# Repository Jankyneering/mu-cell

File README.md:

<h1 align="center">µCell</h1>

<p align="center">An open-source SDR base station platform for digital and analog voice modes.</p>

Got a board? Start with the [Quick Start Guide](docs/quickStartGuide.md).

---

## Contents

- [What is µCell?](#what-is-µcell)
- [Where to Buy](#where-to-buy)
- [Build Your Own](#build-your-own)
- [How the Software Fits Together](#how-the-software-fits-together)
- [Documentation](#documentation)
- [How to Contribute](#how-to-contribute)
- [Acknowledgements & License](#acknowledgements--license)

---

## What is µCell?

µCell is a software-defined radio base station/repeater/transceiver that runs on a Raspberry Pi.

The µCell BB board puts an SX1255 transceiver, its RF front-end, and a HAT identification EEPROM on a board that sits on a Pi 3, 4, 5, or Zero 2W. A single command installs the driver, and from there you pick the radio software you want to run.

The board presents itself as a standard SoapySDR device. The project started with TETRA, but DMR, D-Star, YSF, P25, and analog FM run on the same board through MMDVM-IQ, and general-purpose SDR software works with it directly. The goal is to support every voice mode we can reach.

Everything is open. Schematics, PCB layouts, production outputs, 3D printed case designs, drivers, and the EEPROM tooling are all in this repository, under licences that let you build, modify, and sell your own.

---

## Where to Buy

Assembled and tested µCell BB boards are sold by Fred Corp., one half of the Jankyneering team:

[store.fredcorp.cc](http://store.fredcorp.cc/)

Each board sold there is individually measured on an RF test set before shipping, and carries a signed EEPROM so the driver can confirm where it came from. See the [FAQ](docs/faq.md) for what signing does and does not mean.

---

## Build Your Own

The design is open and the production outputs are in this repository, ready to upload to a PCBA house. Component choice is critical: the RF path depends on inductor Q, capacitor dielectric, and a low drift referenceL. Foregoing proper part selection will affect sensitivity and output power.

See [docs/muCellBBManufacture.md](docs/muCellBBManufacture.md) for the production package contents, the stackup, the component selection notes, and the EEPROM writing procedure.

---

## Software structure

The stack has three layers.

### 1. µCell BB drivers

[mu-cell-bb-drivers](https://github.com/Jankyneering/mu-cell-bb-drivers) contains the device tree overlay that makes the Pi recognise the board, and `SoapyMuCell`, the hardware driver itself. The install script in this repository builds and installs both.

### 2. SoapySDR

`SoapyMuCell` registers with SoapySDR as the device `driver=mucell`. Any SoapySDR-aware application can open the board without knowing anything about the SX1255. This is the integration point: adding support for new software is usually a matter of pointing it at the right device string.

### 3. Applications

| Software | Modes | Status |
|---|---|---|
| [Flowstation](https://github.com/razvanzeces/flowstation) | TETRA, wider feature set, less stable | Supported |
| [Tetra-Bluestation](https://github.com/MidnightBlueLabs/tetra-bluestation) | TETRA, stable, fewer features | Supported on the testing branch, landing in main |
| [Nexus-BS](https://github.com/invictus737/nexus-bs/) | TETRA, different development direction than Flowstation | Untested, but claims support |
| [MMDVM-IQ](https://github.com/g4klx/MMDVM-IQ) | FM, DMR, D-Star, YSF, P25, POCSAG | Supported |

<!-- TODO: confirm the Bluestation branch wording, and whether MMDVM-IQ is "in progress" or already usable -->

Each of these is its own project with its own installation instructions. 
General-purpose SDR software reaches the board the same way, through the `driver=mucell` device string:

| Software | Status |
|---|---|
| [GQRX](https://www.gqrx.dk/) | Supported |
| [CubicSDR](https://cubicsdr.com/) | Supported |
| [GNU Radio](https://www.gnuradio.org/) | Should work through the Soapy blocks, more testing needed |
| [SDR++](https://www.sdrpp.org/) | Needs a dedicated source module, not yet written |

The [quick start guide](docs/quickStartGuide.md) covers how to point each one at the board.

---

## Documentation

| Document | Covers |
|---|---|
| [Quick Start Guide](docs/quickStartGuide.md) | Flash a Pi, install the driver, set up your radio software, get on air |
| [Building the Drivers](docs/buildDriver.md) | The driver and overlay built by hand, step by step, no scripts |
| [Hardware](docs/hardware.md) | Board specifications, connectors, measured performance, cases, roadmap |
| [Manufacturing](docs/muCellBBManufacture.md) | Production outputs, component selection, EEPROM writing and signing |
| [FAQ](docs/faq.md) | Common questions, support routes, the "not genuine" warning |

---

## How to Contribute

Contributions are welcome. For small fixes or documentation updates, feel free to open a pull request directly. For larger changes, open an issue first so the approach can be discussed. Keep pull requests focused and include a clear description of what changed and why.

Hardware contributions follow the same route. If you are proposing a layout or component change, include the reasoning and, where relevant, the measurements that back it up.

Support for a new mode or a new piece of SDR software is always of interest. If you get something working against `driver=mucell`, a short section for the quick start guide is a welcome contribution on its own.

---

## Acknowledgements & License

µCell builds on the work of several open-source projects:

- Tatu Peltola ([tejeez](https://github.com/tejeez/)), designer of the [SXCeiver](https://github.com/tejeez/sxxcvr), which provided early inspiration for compact SX1255-based SDR hardware.
- Wouter Bokslag ([Midnight Blue](https://github.com/MidnightBlueLabs/)) and contributors, authors of [TETRA-bluestation](https://github.com/MidnightBlueLabs/tetra-bluestation), which implements an open TETRA base station stack.

We also acknowledge the broader SDR and SoapySDR communities whose work enables hardware experimentation with modern radio systems.

Certified open source hardware by OSHWA under registration BE000024

<!-- TODO: download the certification mark with the UID from the project page at certification.oshwa.org/be000024.html and commit it to docs/logos/. The link above assumes oshw-be000024.svg. -->

Hardware and documentation published under CreativeCommons BY-SA 4.0

[Creative Commons Attribution-ShareAlike 4.0 International License](http://creativecommons.org/licenses/by-sa/4.0/)

Software published under GNU GPLv3

[GNU GPLv3](https://www.gnu.org/licenses/gpl-3.0.en.html)

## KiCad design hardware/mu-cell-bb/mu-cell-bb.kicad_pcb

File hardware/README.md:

# Hardware

Folder containing hardware design files, schematics, and documentation for the hardware side of the project.

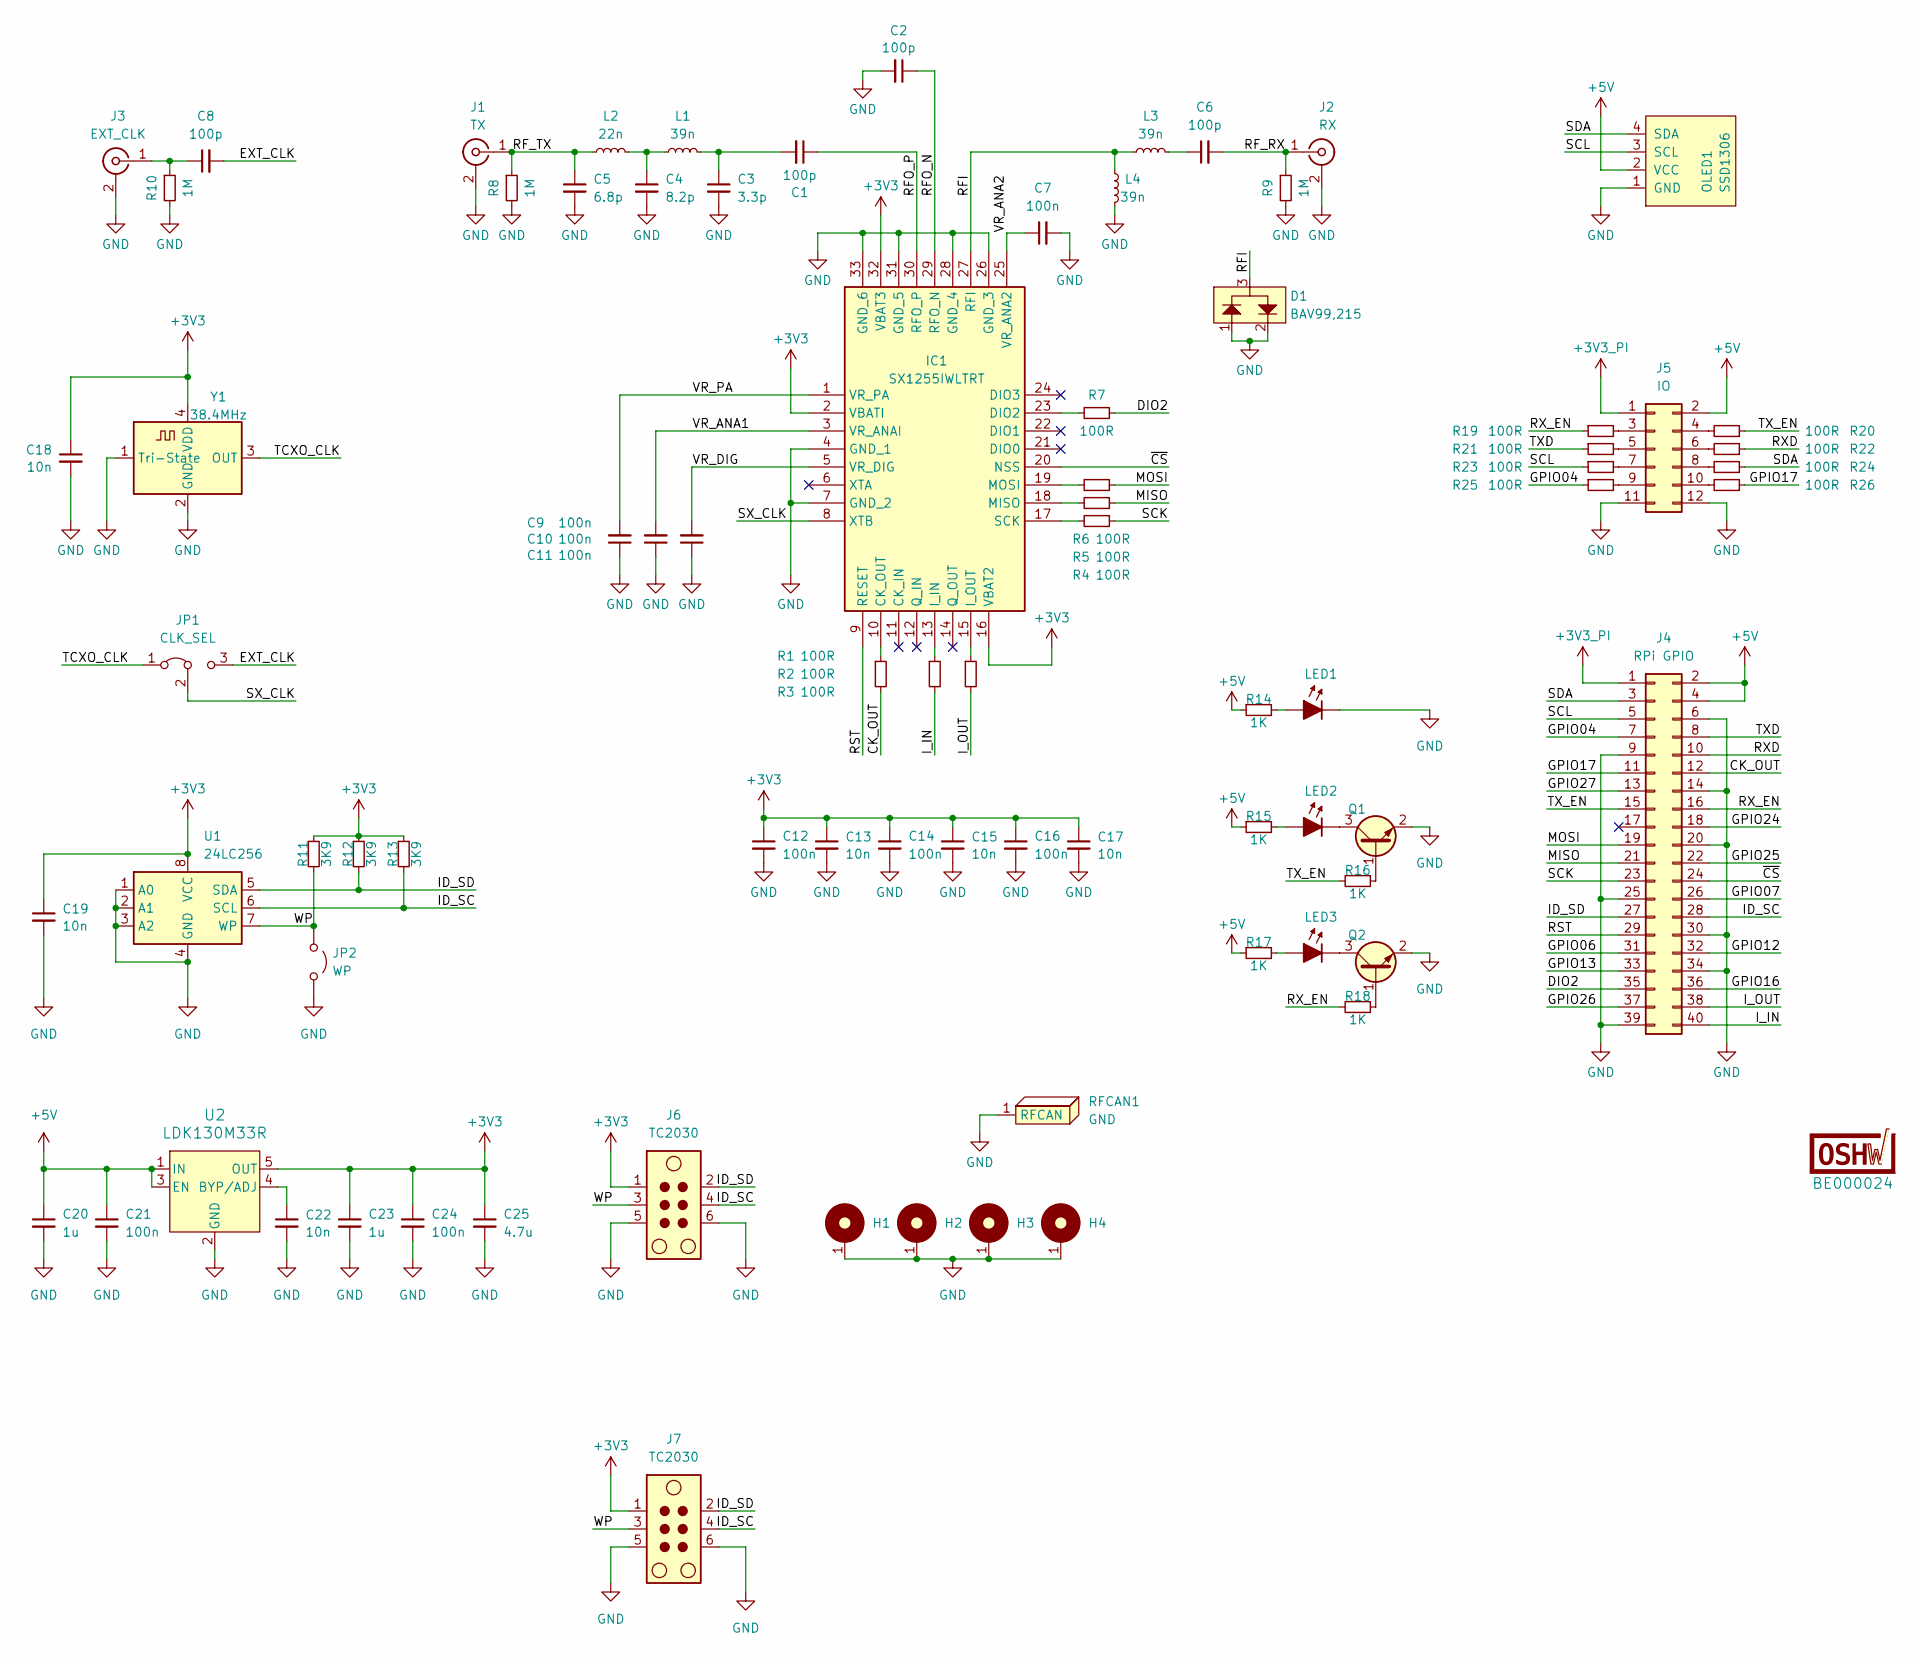
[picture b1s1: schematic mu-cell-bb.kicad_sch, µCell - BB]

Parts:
BE000024: OSHW-Certification-Mark-Stacked_8x7mm_SilkMask
C1, C2, C6, C8: 100p; C_0402_1005Metric_Pad0.74x0.62mm_HandSolder; MPN GCM1555C1H101FA16D; LCSC Part C2941926
C3: 3.3p; C_0402_1005Metric_Pad0.74x0.62mm_HandSolder; MPN GCM1555C1H3R3GA16D; LCSC Part C2941931
C4: 8.2p; C_0402_1005Metric_Pad0.74x0.62mm_HandSolder; MPN 0402CG8R2G500NT; LCSC Part C2857971
C5: 6.8p; C_0402_1005Metric_Pad0.74x0.62mm_HandSolder; MPN GCM1555C1H6R8FA16D; LCSC Part C1864373
C7, C9, C10, C11, C12, C14, C16, C21, C24: 100n; C_0402_1005Metric_Pad0.74x0.62mm_HandSolder; MPN CC0402KRX7R7BB104; LCSC Part C60474
C13, C15, C17, C18, C19, C22: 10n; C_0402_1005Metric_Pad0.74x0.62mm_HandSolder; MPN CC0402KRX7R9BB103; LCSC Part C60133
C20, C23: 1u; C_0402_1005Metric_Pad0.74x0.62mm_HandSolder; MPN CL05A105KO5NNNC; LCSC Part C29266
C25: 4.7u; C_0402_1005Metric_Pad0.74x0.62mm_HandSolder; MPN CL05A475MP5NRNC; LCSC Part C23733
D1: BAV99,215; SOT-23-3; MPN BAV99,215; LCSC Part C2500
H1, H2, H3, H4: MountingHole_M3_3.2mm_Pad; MountingHole_3.2mm_Pad
IC1: SX1255IWLTRT; QFN50P500X500X80-33N-D; Mouser Part Number 947-SX1255IWLTRT
J1: TX; U.FL_Vertical_Passthrough; MPN BWU.FL-IPEX1; LCSC Part C5137195
J2: RX; U.FL_Vertical_Passthrough; MPN BWU.FL-IPEX1; LCSC Part C5137195
J3: EXT_CLK; U.FL_Vertical_GND; MPN BWU.FL-IPEX1; LCSC Part C5137195
J4: RPi GPIO; PinSocket_2x20_P2.54mm_Vertical
J5: IO; IDC-Header_2x06_P2.54mm_Horizontal
J6, J7: TC2030; Tag-Connect_TC2030-IDC-NL_2x03_P1.27mm_Vertical
JP1: CLK_SEL; SolderJumper-3_P1.3mm_Bridged12_RoundedPad1.0x1.5mm_NumberL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
JP2: WP; SolderJumper-2_P1.3mm_Open_RoundedPad1.0x1.5mm
L1, L3, L4: 39n; L_0402_1005Metric_Pad0.77x0.64mm_HandSolder; MPN 0402CS-39NXGRW; LCSC Part C40399699
L2: 22n; L_0402_1005Metric_Pad0.77x0.64mm_HandSolder; MPN 0402CS-22NXGRW; LCSC Part C22440906
LED1: Red; LED_0402_1005Metric_Pad0.77x0.64mm; MPN F.0402.00003/P2-0402R1TS2-045T-001; LCSC Part C7496803
LED2: Amber; LED_0402_1005Metric_Pad0.77x0.64mm; MPN BL-HJC37A-AV-TRB; LCSC Part C5123495
LED3: Green; LED_0402_1005Metric_Pad0.77x0.64mm; MPN 16-213/GHC-YR1S1/3T; LCSC Part C74338
OLED1: SSD1306; OLED_128x64_I2C
Q1, Q2: BC817-40W; SOT-323_SC-70; MPN LBC817-40WT1G; LCSC Part C383187
R1, R2, R3, R4, R5, R6, R7, R19, R20, R21, R22, R23, R24, R25, R26: 100R; R_0402_1005Metric_Pad0.72x0.64mm_HandSolder; MPN RC0402FR-07100RL; LCSC Part C106232
R8, R9, R10: 1M; R_0402_1005Metric_Pad0.72x0.64mm_HandSolder; MPN 0402WGF1004TCE; LCSC Part C26083
R11, R12, R13: 3K9; R_0402_1005Metric_Pad0.72x0.64mm_HandSolder; MPN FRC0402F3901TS; LCSC Part C2909346
R14, R15, R16, R17, R18: 1K; R_0402_1005Metric_Pad0.72x0.64mm_HandSolder; MPN RC0402FR-071KL; LCSC Part C106235
RFCAN1: GND; 2118707-4 CAN; MPN 2118707-4; LCSC Part C22418535
U1: 24LC256; SOIC-8_3.9x4.9mm_P1.27mm; MPN 24LC256-E/SN; LCSC Part C615210
U2: LDK130M33R; SOT23-5L_1P75X3P05X0P95_STM; MPN LDK130M33R; LCSC Part C2969807
Y1: 38.4MHz; Crystal_SMD_2016-4Pin_2.0x1.6mm; MPN TG2016SMN 38.4000M-MCGNNM3; LCSC Part C1987359

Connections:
+3V3: C12.1, C13.1, C14.1, C15.1, C16.1, C17.1, C18.1, C19.1, C23.1, C24.1, C25.1, IC1.2 (VBATI), IC1.16 (VBAT2), IC1.32 (VBAT3), J6.1, J7.1, R11.1, R12.1, R13.1, U1.8 (VCC), U2.5 (OUT), Y1.4 (VDD)
+3V3_PI: J4.1, J5.1
+5V: C20.1, C21.1, J4.2, J4.4, J5.2, OLED1.2 (VCC), R14.1, R15.1, R17.1, U2.1 (IN), U2.3 (EN)
/CK_OUT: J4.12, R1.2
/DIO2: J4.35, R7.1
/EXT_CLK: C8.2, JP1.3 (B)
/GPIO04: J4.7, R25.1
/GPIO06: J4.31
/GPIO07: J4.26
/GPIO12: J4.32
/GPIO13: J4.33
/GPIO16: J4.36
/GPIO17: J4.11, R26.1
/GPIO24: J4.18
/GPIO25: J4.22
/GPIO26: J4.37
/GPIO27: J4.13
/ID_SC: J4.28, J6.4, J7.4, R13.2, U1.6 (SCL)
/ID_SD: J4.27, J6.2, J7.2, R12.2, U1.5 (SDA)
/I_IN: J4.40, R2.2
/I_OUT: J4.38, R3.2
/MISO: J4.21, R5.1
/MOSI: J4.19, R6.1
/RFI: D1.3, IC1.27 (RFI), L3.2, L4.2
/RFO_N: C2.1, IC1.29 (RFO_N)
/RFO_P: C1.1, IC1.30 (RFO_P)
/RF_RX: C6.2, J2.1 (In), R9.1
/RF_TX: C5.1, J1.1 (In), L2.2, R8.1
/RST: IC1.9 (RESET), J4.29
/RXD: J4.10, R22.1
/RX_EN: J4.16, R18.2, R19.1
/SCK: J4.23, R4.1
/SCL: J4.5, OLED1.3 (SCL), R23.1
/SDA: J4.3, OLED1.4 (SDA), R24.1
/SX_CLK: IC1.8 (XTB), JP1.2 (C)
/TCXO_CLK: JP1.1 (A), Y1.3 (OUT)
/TXD: J4.8, R21.1
/TX_EN: J4.15, R16.2, R20.1
/VR_ANA1: C10.2, IC1.3 (VR_ANAI)
/VR_ANA2: C7.1, IC1.25 (VR_ANA2)
/VR_DIG: C11.2, IC1.5 (VR_DIG)
/VR_PA: C9.2, IC1.1 (VR_PA)
/WP: J6.3, J7.3, JP2.1 (A), R11.2, U1.7 (WP)
/~CS: IC1.20 (NSS), J4.24
GND: C2.2, C3.2, C4.2, C5.2, C7.2, C9.1, C10.1, C11.1, C12.2, C13.2, C14.2, C15.2, C16.2, C17.2, C18.2, C19.2, C20.2, C21.2, C22.2, C23.2, C24.2, C25.2, D1.1, D1.2, H1.1, H2.1, H3.1, H4.1, IC1.4 (GND_1), IC1.7 (GND_2), IC1.26 (GND_3), IC1.28 (GND_4), IC1.31 (GND_5), IC1.33 (GND_6), J1.2 (Ext), J2.2 (Ext), J3.2 (Ext), J4.6, J4.9, J4.14, J4.20, J4.25, J4.30, J4.34, J4.39, J5.11, J5.12, J6.5, J6.6, J7.5, J7.6, JP2.2 (B), L4.1, LED1.1 (K), OLED1.1 (GND), Q1.2 (E), Q2.2 (E), R8.2, R9.2, R10.2, RFCAN1.1 (RFCAN_1), U1.1 (A0), U1.2 (A1), U1.3 (A2), U1.4 (GND), U2.2 (GND), Y1.1 (Tri-State), Y1.2 (GND)
unnamed: C1.2, C3.1, L1.1
unnamed: C4.1, L1.2, L2.1
unnamed: C6.1, L3.1
unnamed: IC1.10 (CK_OUT), R1.1
unnamed: IC1.23 (DIO2), R7.2
unnamed: IC1.13 (I_IN), R2.1
unnamed: IC1.15 (I_OUT), R3.1
unnamed: IC1.18 (MISO), R5.2
unnamed: IC1.19 (MOSI), R6.2
unnamed: IC1.17 (SCK), R4.2
unnamed: C8.1, J3.1 (In), R10.1
unnamed: J5.3, R19.2
unnamed: J5.4, R20.2
unnamed: J5.5, R21.2
unnamed: J5.6, R22.2
unnamed: J5.7, R23.2
unnamed: J5.8, R24.2
unnamed: J5.9, R25.2
unnamed: J5.10, R26.2
unnamed: LED1.2 (A), R14.2
unnamed: LED2.2 (A), R15.2
unnamed: LED2.1 (K), Q1.3 (C)
unnamed: LED3.2 (A), R17.2
unnamed: LED3.1 (K), Q2.3 (C)
unnamed: Q1.1 (B), R16.1
unnamed: Q2.1 (B), R18.1
unnamed: C22.1, U2.4 (BYP/ADJ)

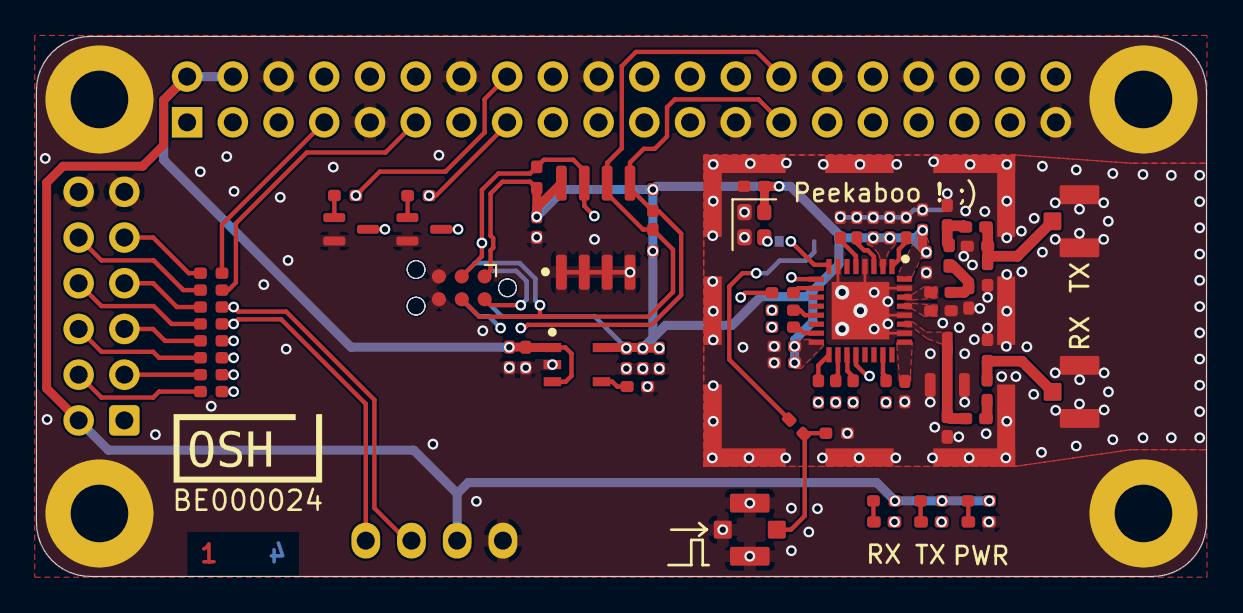
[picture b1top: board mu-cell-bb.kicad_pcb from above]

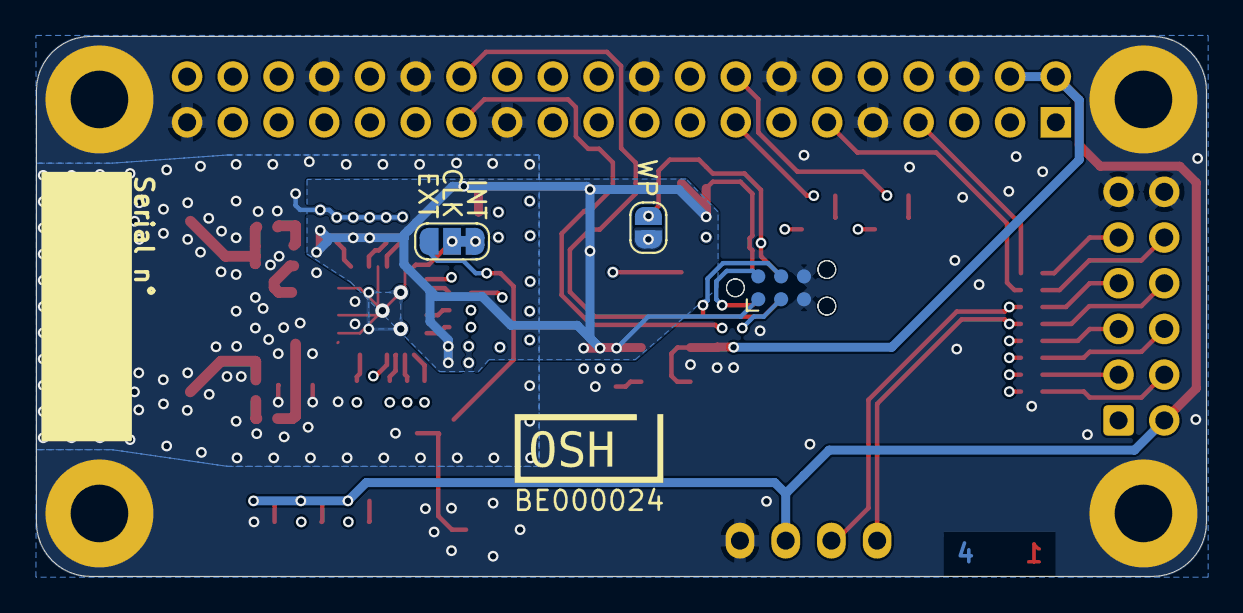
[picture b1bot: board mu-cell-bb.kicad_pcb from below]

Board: 4 copper layers, 65.0 x 30.0 mm, 82 parts (5 on the bottom side), 63 nets.

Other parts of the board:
BE000024#2: OSHW-Certification-Mark-Stacked_8x7mm_SilkMask

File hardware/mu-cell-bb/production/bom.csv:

Designator,Footprint,Quantity,Value,LCSC Part #
"C1, C2, C6, C8",0402,4,100p,C2941926
"C10, C11, C12, C14, C16, C21, C24, C7, C9",0402,9,100n,C60474
"C13, C15, C17, C18, C19, C22",0402,6,10n,C60133
"C20, C23",0402,2,1u,C29266
C25,0402,1,4.7u,C23733
C3,0402,1,3.3p,C2941931
C4,0402,1,8.2p,C2857971
C5,0402,1,6.8p,C1864373
D1,SOT-23-3,1,"BAV99,215",C2500
IC1,QFN50P500X500X80-33N-D,1,SX1255IWLTRT,C89372
J1,U.FL_Vertical_Passthrough,1,TX,C5137195
J2,U.FL_Vertical_Passthrough,1,RX,C5137195
J3,U.FL_Vertical_GND,1,EXT_CLK,C5137195
"L1, L3, L4",0402,3,39n,C40399699
L2,0402,1,22n,C22440906
LED1,0402,1,Red,C7496803
LED2,0402,1,Amber,C5123495
LED3,0402,1,Green,C74338
"Q1, Q2",SOT-323_SC-70,2,BC817-40W,C383187
"R1, R19, R2, R20, R21, R22, R23, R24, R25, R26, R3, R4, R5, R6, R7",0402,15,100R,C106232
"R10, R8, R9",0402,3,1M,C26083
"R11, R12, R13",0402,3,3K9,C2909346
"R14, R15, R16, R17, R18",0402,5,1K,C106235
RFCAN1,2118707-4 CAN,1,GND,C22418535
U1,SOIC-8_3.9x4.9mm_P1.27mm,1,24LC256,C615210
U2,SOT23-5L_1P75X3P05X0P95_STM,1,LDK130M33R,C2969807
Y1,Oscillator_SMD_ECS_2520MV-xxx-xx-4Pin_2.5x2.0mm,1,38.4MHz,C1987359

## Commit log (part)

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2026-03-02 added base git repo files
2026-03-02 added `sxxcvr` submodule
2026-03-02 updated `sxxcvr`
2026-03-02 moved submodule into dedicated folder
2026-03-02 added software readme
2026-03-02 added SX1255 dev hat as submodule
2026-03-02 updated submodule
2026-03-03 Added schematics for mu-Cell BB
2026-03-03 added gitignore for KiCAD files
2026-03-03 updated gitignore
2026-03-03 updated schematic
2026-03-03 added tetra-bluestation submodule
2026-03-03 started work on PCB
2026-03-03 added symbols, worked on PCB
2026-03-03 added parts
2026-03-03 Added footprint for SX
2026-03-03 added PCB changes and parts
2026-03-03 moved files
2026-03-03 updated footprints
2026-03-04 Routed majority of components
2026-03-04 added GNU GPLv3 License for software
2026-03-04 added LCSC parts, finished routing
2026-03-04 added template for readme structure
2026-03-04 Cosmetic fixes
2026-03-04 linted readme, moved stuff on PCB
2026-03-04 added sim files
2026-03-04 added Logo
2026-03-04 saved changes on PCB
2026-03-04 added TX and RX front end simulations
2026-03-05 late night PCB changes
2026-03-05 updated silkscreens on PCB
2026-03-07 updated RX an TX front end
2026-03-08 updated sim data
2026-03-08 updated TX and RX front ends
2026-03-08 updated PCB
2026-03-10 added eeprom programming header, updated part numbers
2026-03-10 pulled commits for tetra-bluestation
2026-03-10 made final changes before ordering first batch
2026-03-10 added fabrication output for manufacturing
2026-03-30 migrated to KiCAD 10.0
2026-04-16 added muCell-BB v1.0 folder
2026-04-16 updated tetra-bluestation submodule
2026-04-16 added history folder to gitignore
2026-04-22 added custom overlay for µCell BB
2026-04-22 added build directory to gitignore
2026-04-27 updated makefile for hat EEPROM binary, added public key for RSA check of signed EEPROM
2026-04-27 added base files for SoapyMuCell driver Directly inspired from SoapySX, adding signature checks for µCell BB Hats
2026-04-27 added SoapyMuCell README
2026-04-28 added trailing blank line
2026-04-28 updatet errors in driver sources
2026-04-28 Fix version.sh executable bit
2026-04-28 Update EEPROM parsing logic and adjust version.sh permissions
2026-04-28 fix bit again
2026-04-29 added muCell-BB v1.1 files
2026-04-29 enhanced EEPROM parsing logic and add driver alias registration for SoapyMuCell
2026-04-29 refactor EEPROM parsing logic to reconstruct signed payload from device-tree data
2026-04-29 refactor EEPROM parsing logic to improve UUID handling and string encoding
2026-04-29 refactor, AGN, removed `sx` driver label that caused issues with stability
2026-04-29 added a quick INSTALL.md instruction document
2026-05-14 Remove subfolder (now a separate repo)
2026-05-14 added µCell drivers submodule
2026-05-14 Update installation instructions for SoapyMuCell and submodule references
2026-05-14 update submodule, AGN
2026-05-22 added µNeuron submodule
2026-05-22 updated driver commit tag
2026-05-25 Added install script
2026-05-27 added bug report template
2026-05-27 added v1.2 PCB files
2026-05-27 added rudimentary pogo-pin fixture
2026-05-27 added v1.2 to changelog
2026-06-03 Updated readme and install script
2026-06-03 Added pic
2026-06-11 updated drivers
2026-06-11 Fixed typo in update script

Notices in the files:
README.md:
CC BY-SA 4.0
License: GPL v3
